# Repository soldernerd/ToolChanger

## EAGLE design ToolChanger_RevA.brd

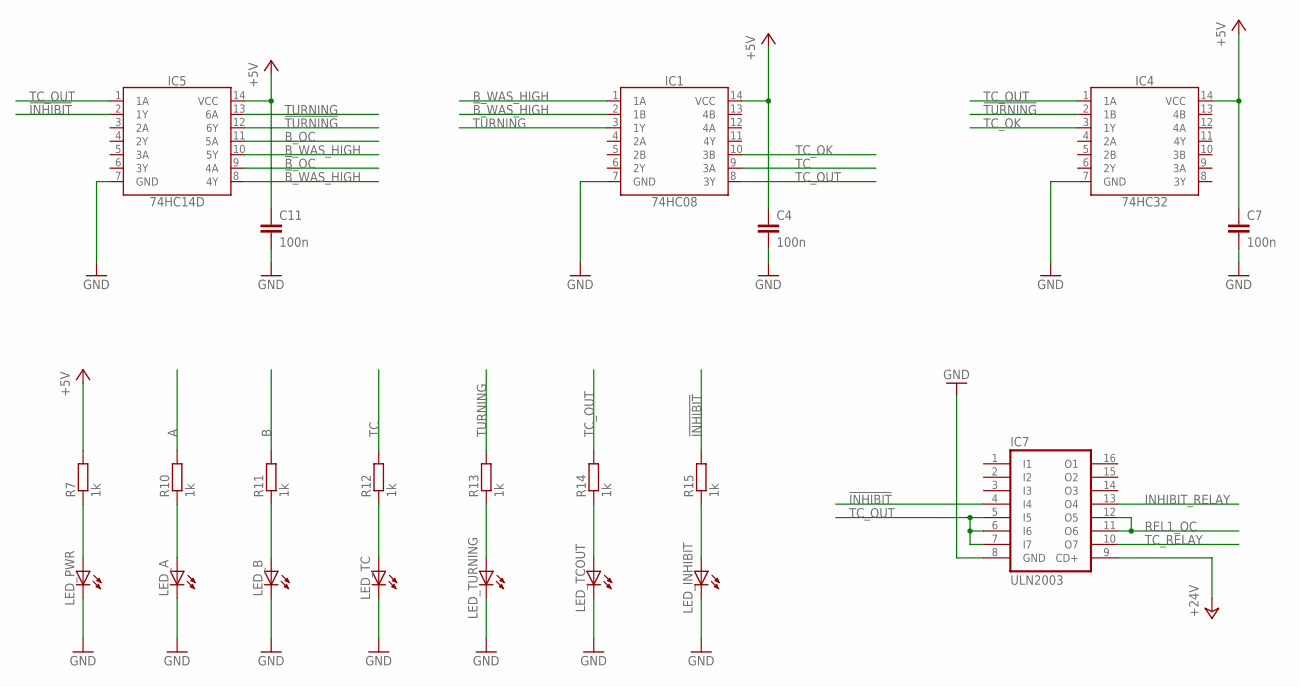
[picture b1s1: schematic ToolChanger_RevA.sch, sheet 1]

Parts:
C4, C7, C11: 100n; C0805
IC1: 74HC08; SO14
IC4: 74HC32; SO14
IC5: 74HC14D; SO14
IC7: ULN2003; SO16
LED_A: LED0805_NB; LED0805_NOBOARDER
LED_B: LED0805_NB; LED0805_NOBOARDER
LED_INHIBIT: LED0805_NB; LED0805_NOBOARDER
LED_PWR: LED0805_NB; LED0805_NOBOARDER
LED_TC: LED0805_NB; LED0805_NOBOARDER
LED_TCOUT: LED0805_NB; LED0805_NOBOARDER
LED_TURNING: LED0805_NB; LED0805_NOBOARDER
R7, R10, R11, R12, R13, R14, R15: 1k; R0805

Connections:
!B!_OC: IC5.9 (4A); also elsewhere on the board
!B!_WAS_HIGH: IC1.2 (1B), IC5.8 (4Y)
!INHIBIT!: IC5.2 (1Y), IC7.4 (I4), R15.2
!TURNING!: IC4.2 (1B), IC5.12 (6Y)
+5V: C4.1, C7.1, C11.1, IC1.14 (VCC), IC4.14 (VCC), IC5.14 (VCC), R7.2; also elsewhere on the board
+24V: IC7.9 (CD+); also elsewhere on the board
A: R10.2; also elsewhere on the board
B: R11.2; also elsewhere on the board
B_OC: IC5.11 (5A); also elsewhere on the board
B_WAS_HIGH: IC1.1 (1A), IC5.10 (5Y)
GND: C4.2, C7.2, C11.2, IC1.7 (GND), IC4.7 (GND), IC5.7 (GND), IC7.8 (GND), LED_A.C, LED_B.C, LED_INHIBIT.C, LED_PWR.C, LED_TC.C, LED_TCOUT.C, LED_TURNING.C; also elsewhere on the board
INHIBIT_RELAY: IC7.13 (O4); also elsewhere on the board
unnamed: LED_PWR.A, R7.1
unnamed: LED_A.A, R10.1
unnamed: LED_B.A, R11.1
unnamed: LED_TC.A, R12.1
unnamed: LED_TURNING.A, R13.1
unnamed: LED_TCOUT.A, R14.1
unnamed: LED_INHIBIT.A, R15.1
REL1_OC: IC7.11 (O6), IC7.12 (O5); also elsewhere on the board
TC: IC1.9 (3A), R12.2; also elsewhere on the board
TC_OK: IC1.10 (3B), IC4.3 (1Y)
TC_OUT: IC1.8 (3Y), IC4.1 (1A), IC5.1 (1A), IC7.5 (I5), IC7.6 (I6), IC7.7 (I7), R14.2
TC_RELAY: IC7.10 (O7); also elsewhere on the board
TURNING: IC1.3 (1Y), IC5.13 (6A), R13.2

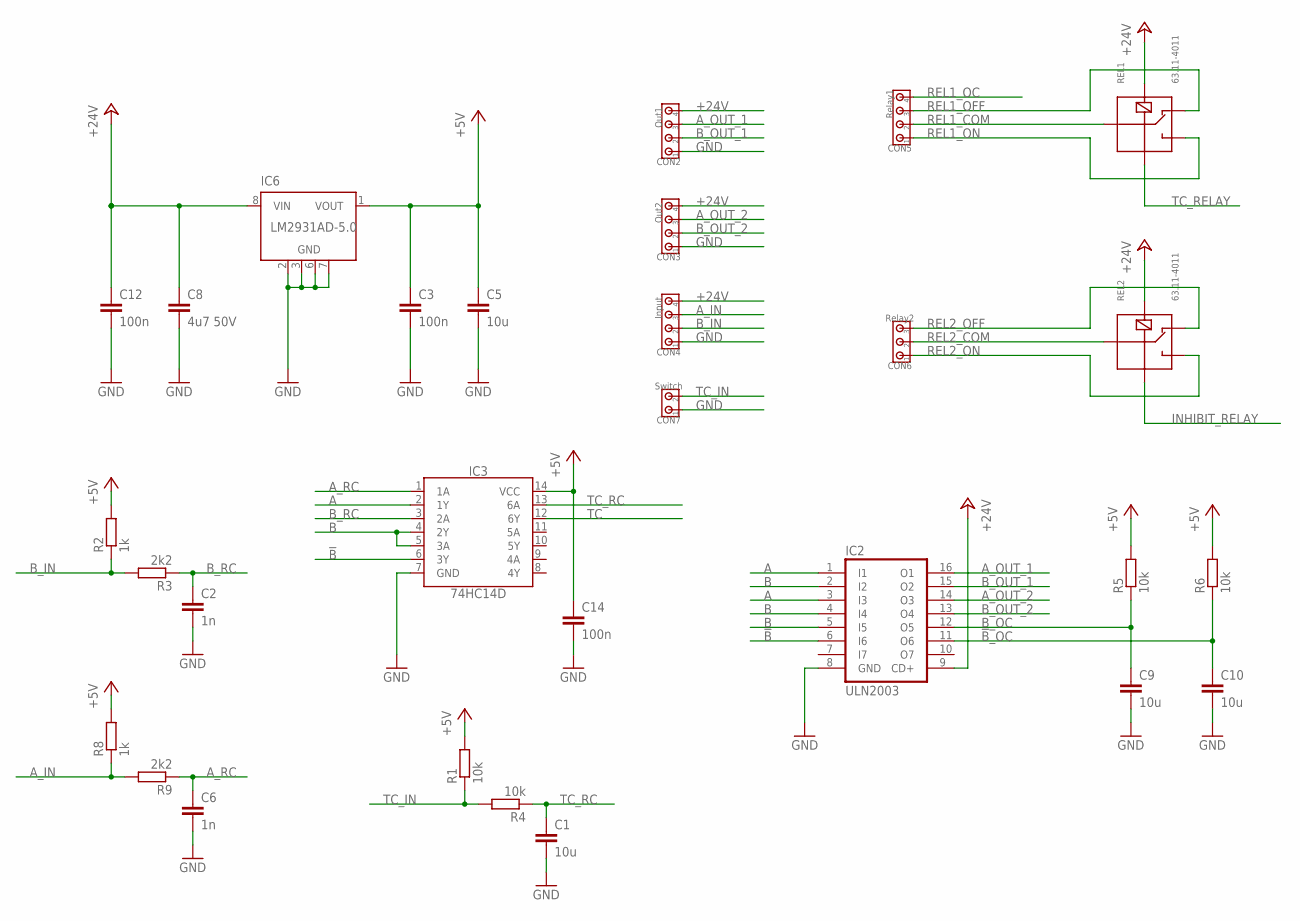
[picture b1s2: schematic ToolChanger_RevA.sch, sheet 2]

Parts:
C1, C5, C9, C10: 10u; C0805
C2, C6: 1n; C0805
C3, C12, C14: 100n; C0805
C8: 4u7 50V; C1206
CON2: Out1; 3.5MM_4X
CON3: Out2; 3.5MM_4X
CON4: Input; 3.5MM_4X
CON5: Relay1; 200MIL_4X
CON6: Relay2; 200MIL_3X
CON7: Switch; 3.5MM_2X
IC2: ULN2003; SO16
IC3: 74HC14D; SO14
IC6: LM2931AD-5.0; SOIC8
R1, R4, R5, R6: 10k; R0805
R2, R8: 1k; R0805
R3, R9: 2k2; R0805
REL1, REL2: 63.11-4011; G5LE

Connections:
!B!: IC2.6 (I6), IC3.6 (3Y)
!B!_OC: C10.1, IC2.11 (O6), R6.1; also elsewhere on the board
+5V: C3.1, C5.1, C14.1, IC3.14 (VCC), IC6.1 (VOUT), R1.2, R2.2, R5.2, R6.2, R8.2; also elsewhere on the board
+24V: C8.1, C12.1, CON2.4, CON3.4, CON4.4, IC2.9 (CD+), IC6.8 (VIN), REL1.2, REL2.2; also elsewhere on the board
A: IC2.1 (I1), IC2.3 (I3), IC3.2 (1Y); also elsewhere on the board
A_IN: CON4.3, R8.1, R9.2
A_OUT_1: CON2.3, IC2.16 (O1)
A_OUT_2: CON3.3, IC2.14 (O3)
A_RC: C6.1, IC3.1 (1A), R9.1
B: IC2.2 (I2), IC2.4 (I4), IC2.5 (I5), IC3.4 (2Y), IC3.5 (3A); also elsewhere on the board
B_IN: CON4.2, R2.1, R3.2
B_OC: C9.1, IC2.12 (O5), R5.1; also elsewhere on the board
B_OUT_1: CON2.2, IC2.15 (O2)
B_OUT_2: CON3.2, IC2.13 (O4)
B_RC: C2.1, IC3.3 (2A), R3.1
GND: C1.2, C2.2, C3.2, C5.2, C6.2, C8.2, C9.2, C10.2, C12.2, C14.2, CON2.1, CON3.1, CON4.1, CON7.1, IC2.8 (GND), IC3.7 (GND), IC6.2 (GND), IC6.3 (GND), IC6.6 (GND), IC6.7 (GND); also elsewhere on the board
INHIBIT_RELAY: REL2.1; also elsewhere on the board
REL1_COM: CON5.2, REL1.COM
REL1_OC: CON5.4; also elsewhere on the board
REL1_OFF: CON5.3, REL1.O
REL1_ON: CON5.1, REL1.C
REL2_COM: CON6.2, REL2.COM
REL2_OFF: CON6.3, REL2.O
REL2_ON: CON6.1, REL2.C
TC: IC3.12 (6Y); also elsewhere on the board
TC_IN: CON7.2, R1.1, R4.2
TC_RC: C1.1, IC3.13 (6A), R4.1
TC_RELAY: REL1.1; also elsewhere on the board

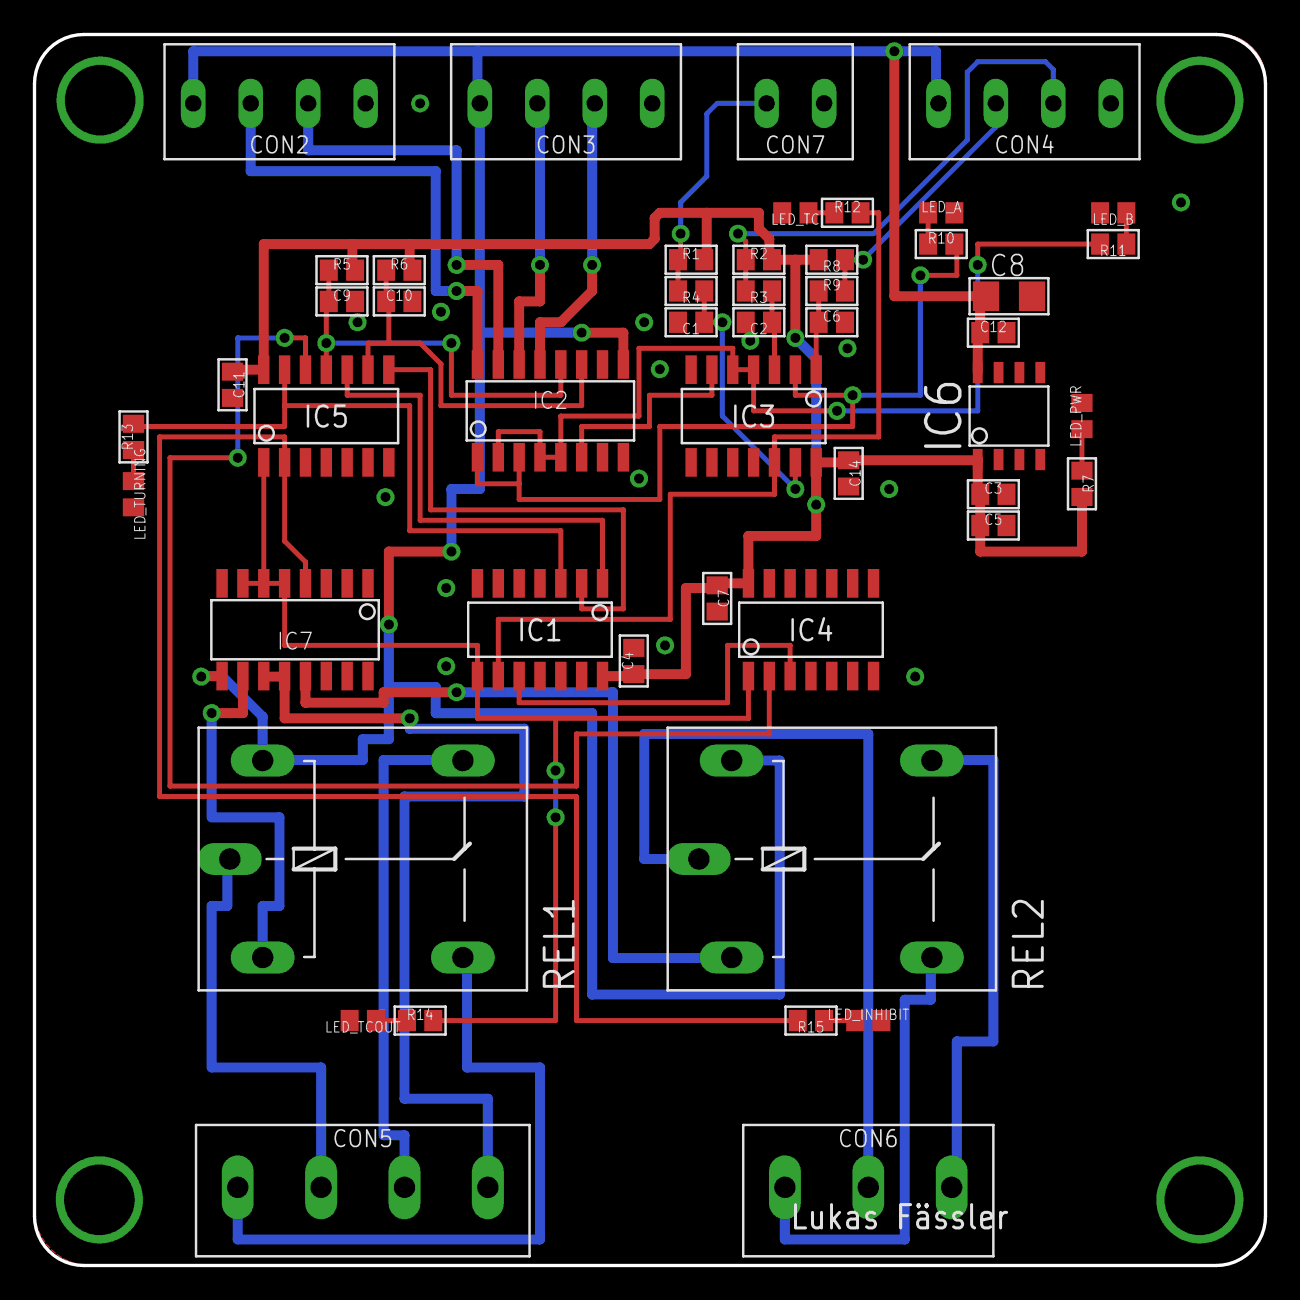
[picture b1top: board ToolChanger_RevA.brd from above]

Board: 2 copper layers, 75.0 x 75.0 mm, 50 parts (0 on the bottom side), 42 nets.

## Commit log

2020-12-08 Initial commit but fully functional
